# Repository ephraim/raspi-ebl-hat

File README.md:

# raspi-ebl-hat
Raspberry Pi Hat for Schaudt EBL 30

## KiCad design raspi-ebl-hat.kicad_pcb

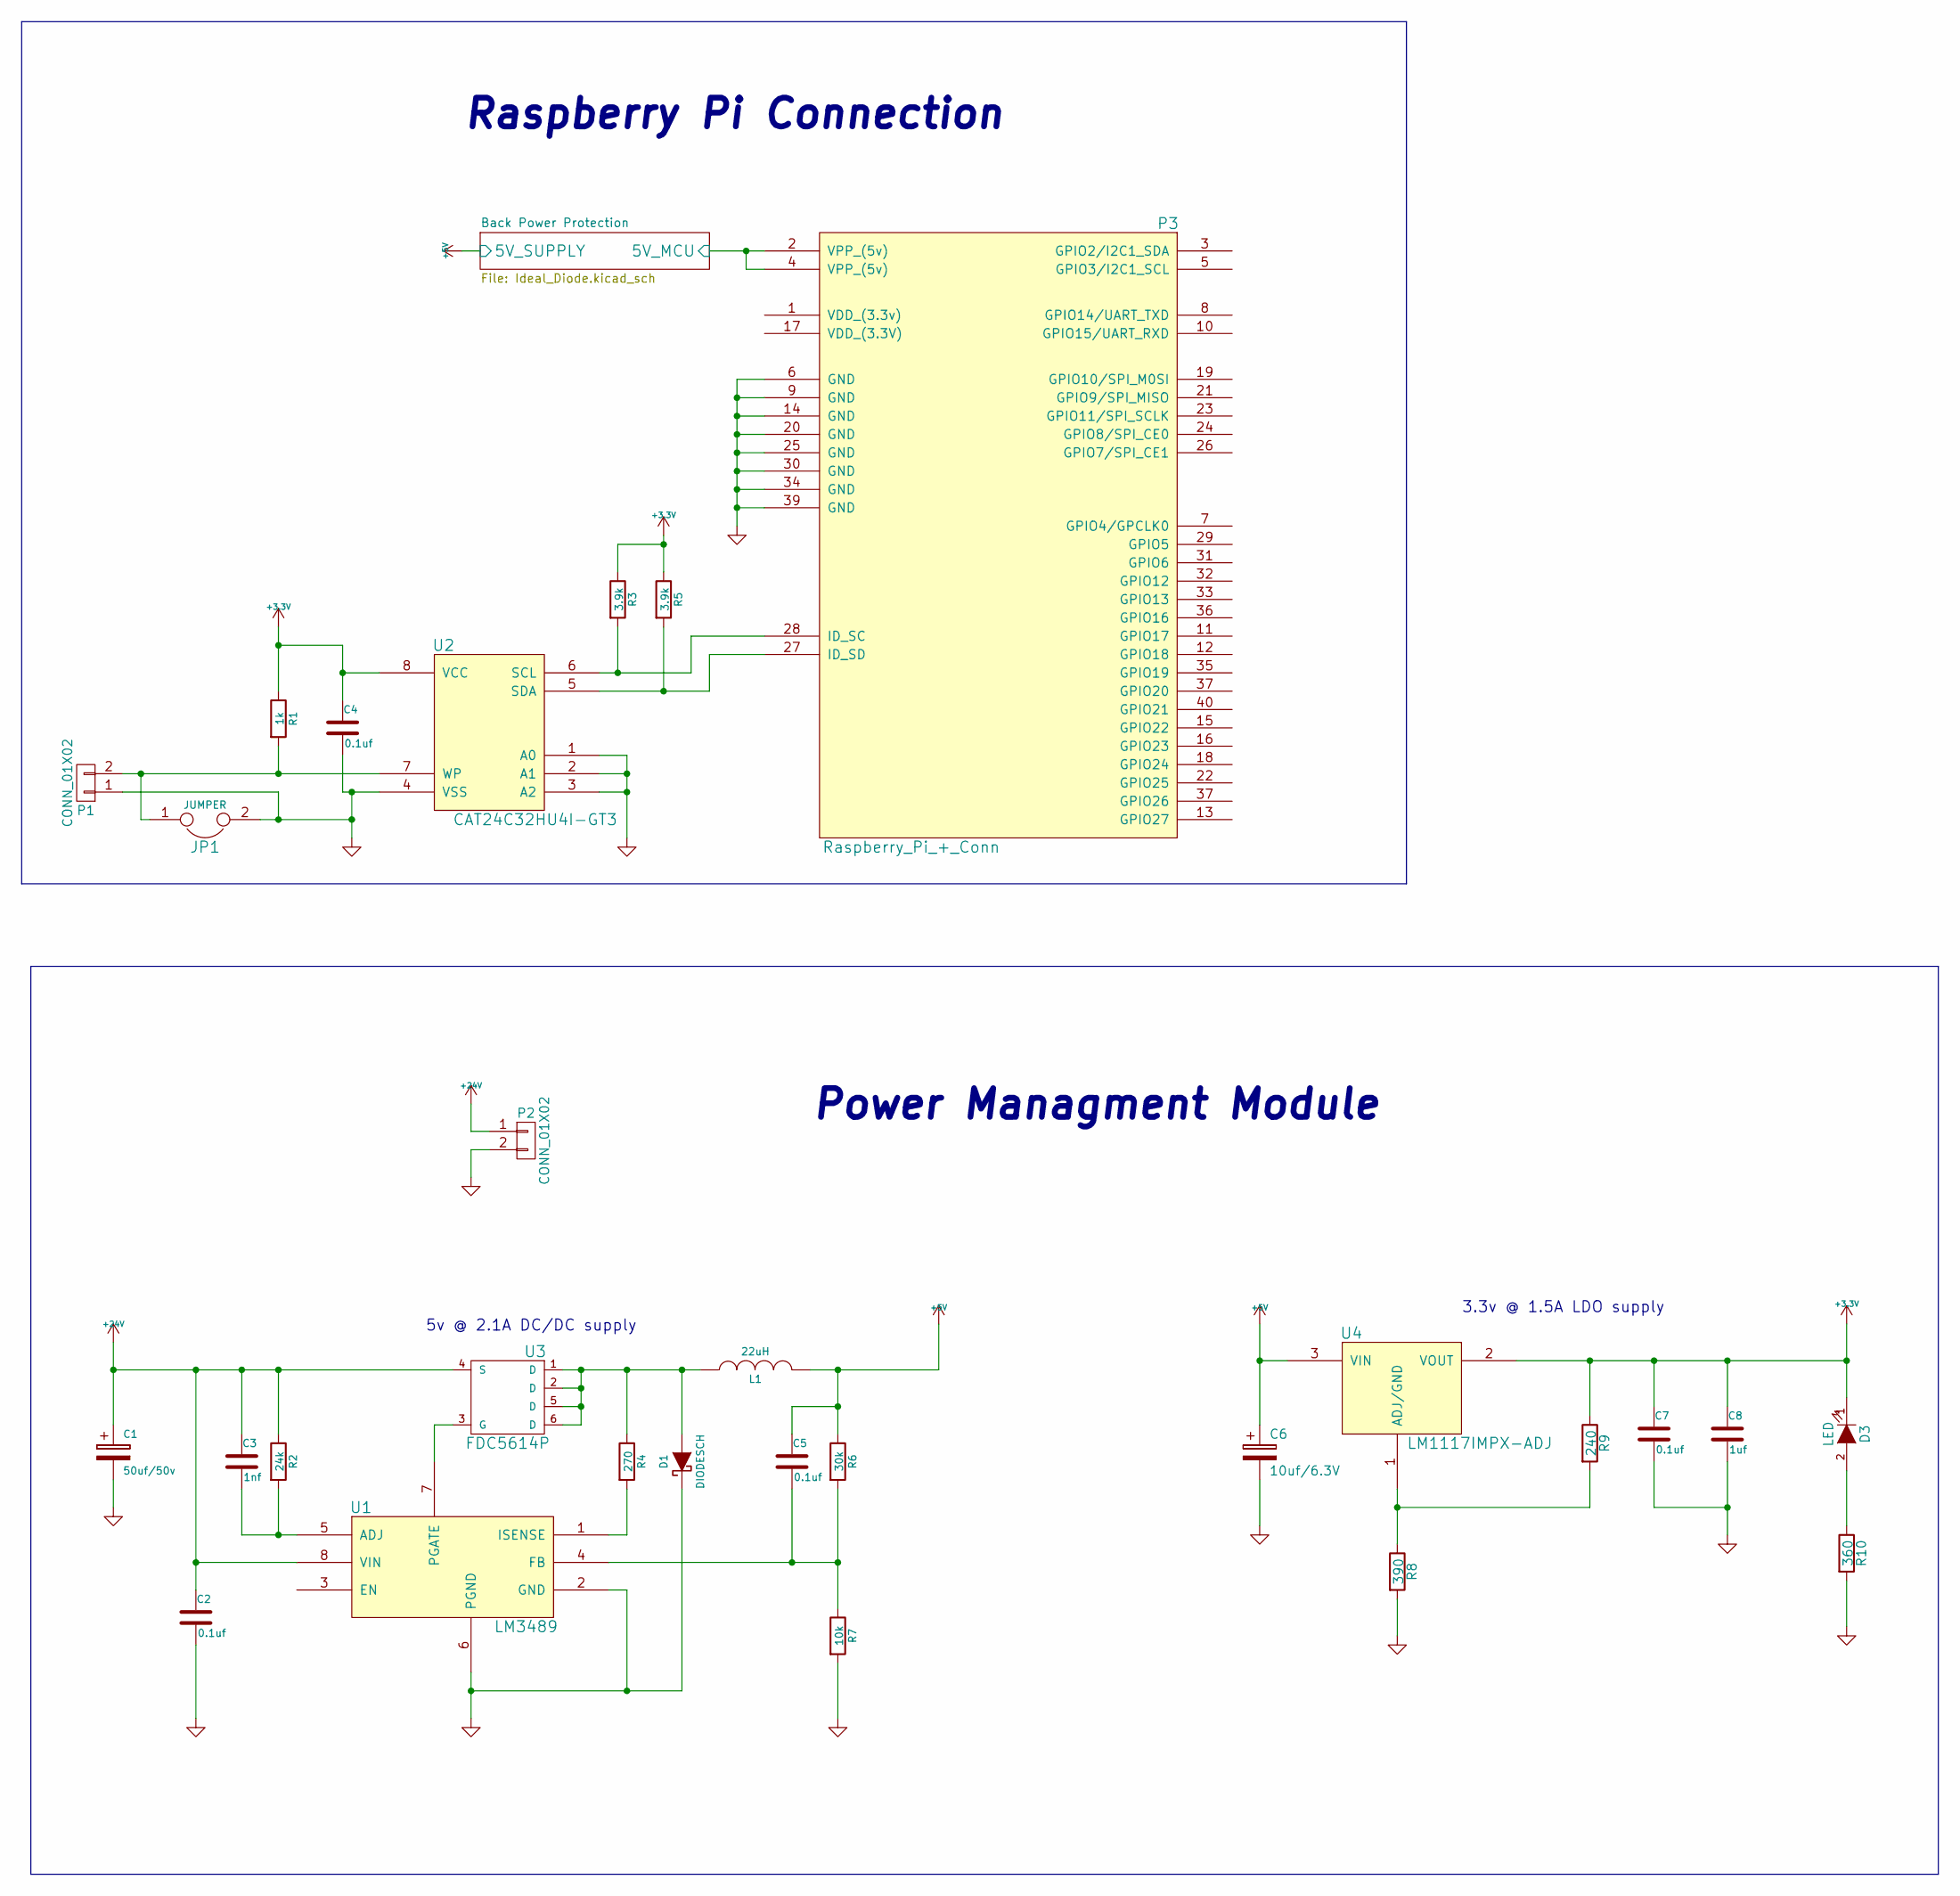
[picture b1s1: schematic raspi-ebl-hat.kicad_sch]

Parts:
C1: 50uf/50v; c_elec_6.3x7.7; Mouser Part No. 647-UUR1H470MCL6GS
C2, C4, C5, C7: 0.1uf; c_0402; Mouser Part No. 810-C1005X5R1H104K
C3: 1nf; c_0402; Mouser Part No. 810-C1005C0G2A102J5C
C6: 10uf/6.3V; c_elec_4x5.3; Mouser Part No. 5985-AVS16V100-F
C8: 1uf; c_0402; Mouser Part No. 810-C1005X5R1H104K
D1: DIODESCH; do214aa; Mouser Part No. 512-MBRS140
D3: LED; Led_0603; Mouser Part No. 743-HT-191USD
JP1: JUMPER; r_0603
L1: 22uH; inductor_smd_8x5mm; Mouser Part No. 652-SRN8040-220M
P1: CONN_01X02; pin_strip_2
P2: CONN_01X02; mkds_1,5-2; Mouser Part No. 651-1904383
P3: Raspberry_Pi_+_Conn; vasch_strip_20x2; Mouser Part No. 517-30340-6002
R1: 1k; r_0402; Mouser Part No. 754-RR0510P-102D
R2: 24k; r_0402; Mouser Part No. 71-CRCW0402-24K-E3
R3, R5: 3.9k; r_0402; Mouser Part No. 71-CRCW04023K90FKED
R4: 270; r_0402; Mouser Part No. 667-ERJ-P6WJ271V
R6: 30k; r_0402; Mouser Part No. 594-MCT06030C3002FP5
R7: 10k; r_0402; Mouser Part No. 71-CRCW0603-10K-E3
R8: 390; r_0402; Mouser Part No. 594-MCT06030C3900FP5
R9: 240; r_0402; Mouser Part No. 754-RR0816P-241D
R10: 360; r_0402; Mouser Part No. 71-CRCW0603316RFKEB
U1: LM3489; msoic-8; Mouser Part No. 926-LM3489MM/NOPB
U2: CAT24C32HU4I-GT3; tssop-8; Mouser Part No. 698-CAT24C32YI-GT3
U3: FDC5614P; sot23-6; Mouser Part No. 512-FDC5614P
U4: LM1117IMPX-ADJ; sot223; Mouser Part No. 926-M1117IMPXADJNOPB

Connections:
+3V3: C4.1, C7.1, C8.1, D3.1 (K), R1.1, R3.1, R5.1, R9.1, U2.8 (VCC), U4.2 (VOUT)
+5V: C5.1, C6.1, L1.2, R6.1, U4.3 (VIN); also elsewhere on the board
+24V: C1.1, C2.1, C3.1, P2.1, R2.1, U1.8 (VIN), U3.4 (S)
/Back Power Protection/5V_MCU: P3.2 (VPP_(5v)), P3.4 (VPP_(5v)); also elsewhere on the board
GND: C1.2, C2.2, C4.2, C6.2, C7.2, C8.2, D1.1 (K), JP1.2, P1.1, P2.2, P3.6 (GND), P3.9 (GND), P3.14 (GND), P3.20 (GND), P3.25 (GND), P3.30 (GND), P3.34 (GND), P3.39 (GND), R7.2, R8.2, R10.2, U1.2 (GND), U1.6 (PGND), U2.1 (A0), U2.2 (A1), U2.3 (A2), U2.4 (VSS); also elsewhere on the board
unnamed: C3.2, R2.2, U1.5 (ADJ)
unnamed: C5.2, R6.2, R7.1, U1.4 (FB)
unnamed: D1.2 (A), L1.1, R4.1, U3.1 (D), U3.2 (D), U3.5 (D), U3.6 (D)
unnamed: D3.2 (A), R10.1
unnamed: JP1.1, P1.2, R1.2, U2.7 (WP)
unnamed: P3.27 (ID_SD), R5.2, U2.5 (SDA)
unnamed: P3.28 (ID_SC), R3.2, U2.6 (SCL)
unnamed: R4.2, U1.1 (ISENSE)
unnamed: R8.1, R9.2, U4.1 (ADJ/GND)
unnamed: U1.7 (PGATE), U3.3 (G)

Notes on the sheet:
3.3v @ 1.5A LDO supply
Power Managment Module
Raspberry Pi Connection
5v @ 2.1A DC/DC supply

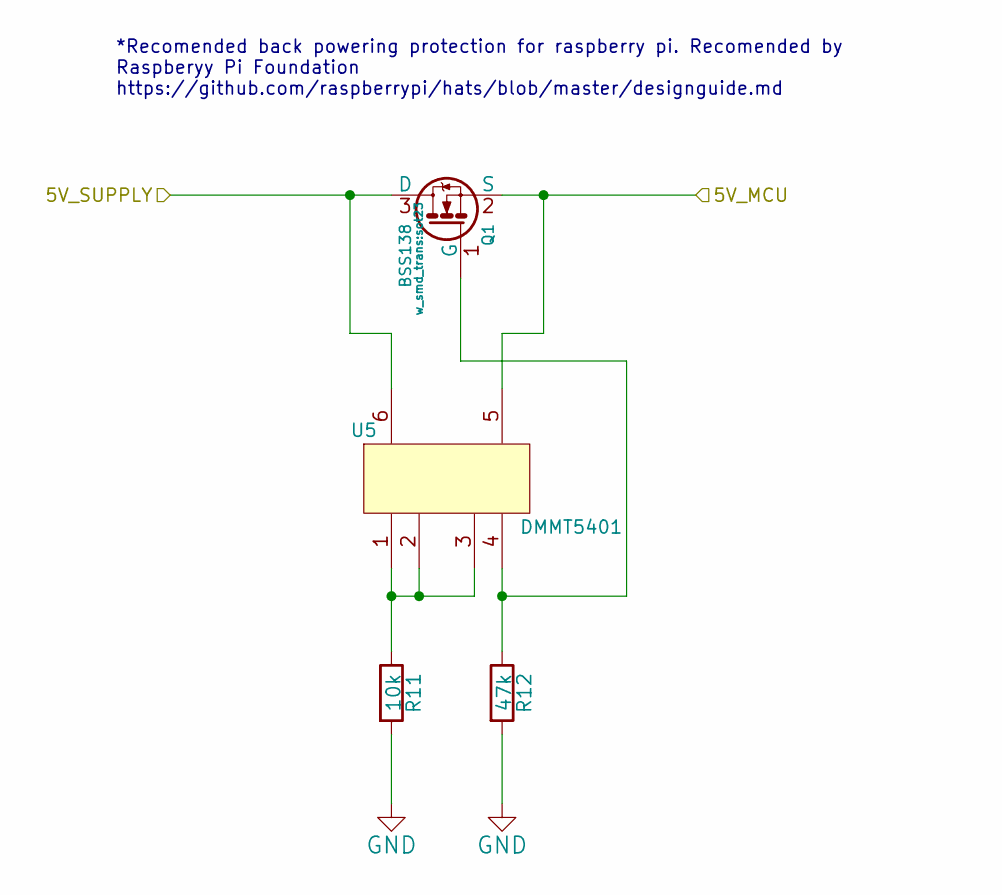
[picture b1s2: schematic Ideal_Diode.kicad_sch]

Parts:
Q1: BSS138; sot23; Mouser Part No. 621-DMG2305UX-13
R11: 10k; r_0402; Mouser Part No. 71-CRCW0402-10K-E3
R12: 47k; r_0402; Mouser Part No. 667-ERJ-2RKF4702X
U5: DMMT5401; sot23-6; Mouser Part No. 621-DMMT5401-7-F

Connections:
+5V: Q1.3 (D), U5.6; also elsewhere on the board
/Back Power Protection/5V_MCU: Q1.2 (S), U5.5; also elsewhere on the board
GND: R11.2, R12.2; also elsewhere on the board
unnamed: Q1.1 (G), R12.1, U5.4
unnamed: R11.1, U5.1, U5.2, U5.3

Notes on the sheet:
*Recomended back powering protection for raspberry pi. Recomended by Raspberyy Pi Foundation https://github.com/raspberrypi/hats/blob/master/designguide.md

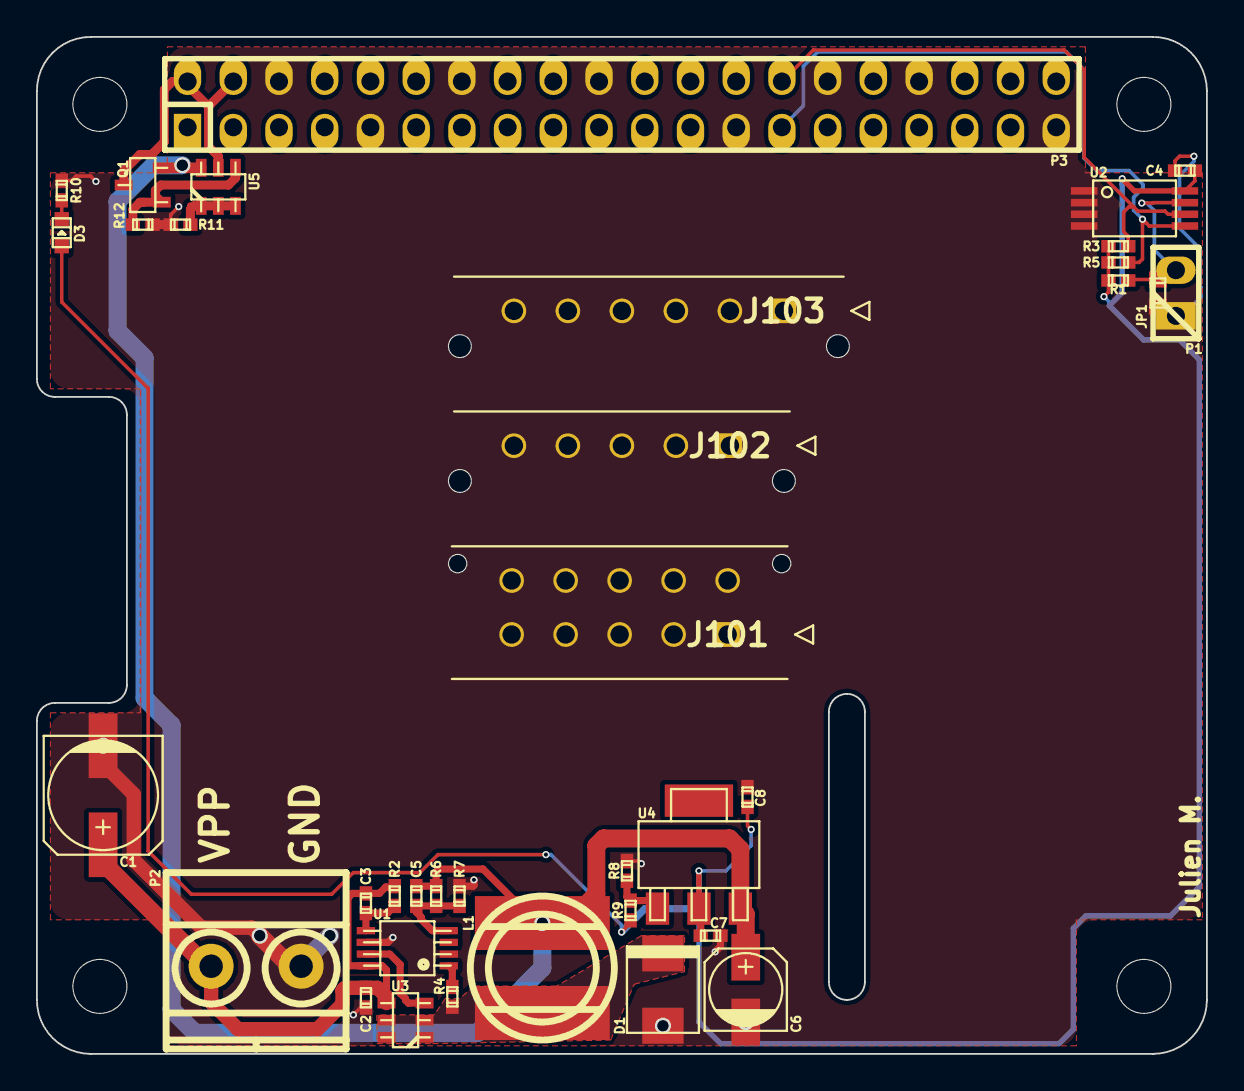
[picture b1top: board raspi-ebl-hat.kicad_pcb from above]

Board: 2 copper layers, 65.0 x 56.5 mm, 36 parts (0 on the bottom side), 17 nets.

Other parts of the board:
J101: 43045-1012; 43045-10YY_12,13,14
J102: 43650-0515; 43650-05YY_15,16,17
J103: 43650-0615; 43650-06YY_15,16,17

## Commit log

2022-03-10 added .gitignore
2022-03-10 cleanup
2022-03-10 added readme
2022-03-21 imported pihat-template stuff
2022-03-21 added EBL header
2022-03-23 fix 3D viewer, at least on linux

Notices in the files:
raspi-ebl-hat.kicad_pcb:
License: CERN OHL V1.2
CERN OHL V1.2
